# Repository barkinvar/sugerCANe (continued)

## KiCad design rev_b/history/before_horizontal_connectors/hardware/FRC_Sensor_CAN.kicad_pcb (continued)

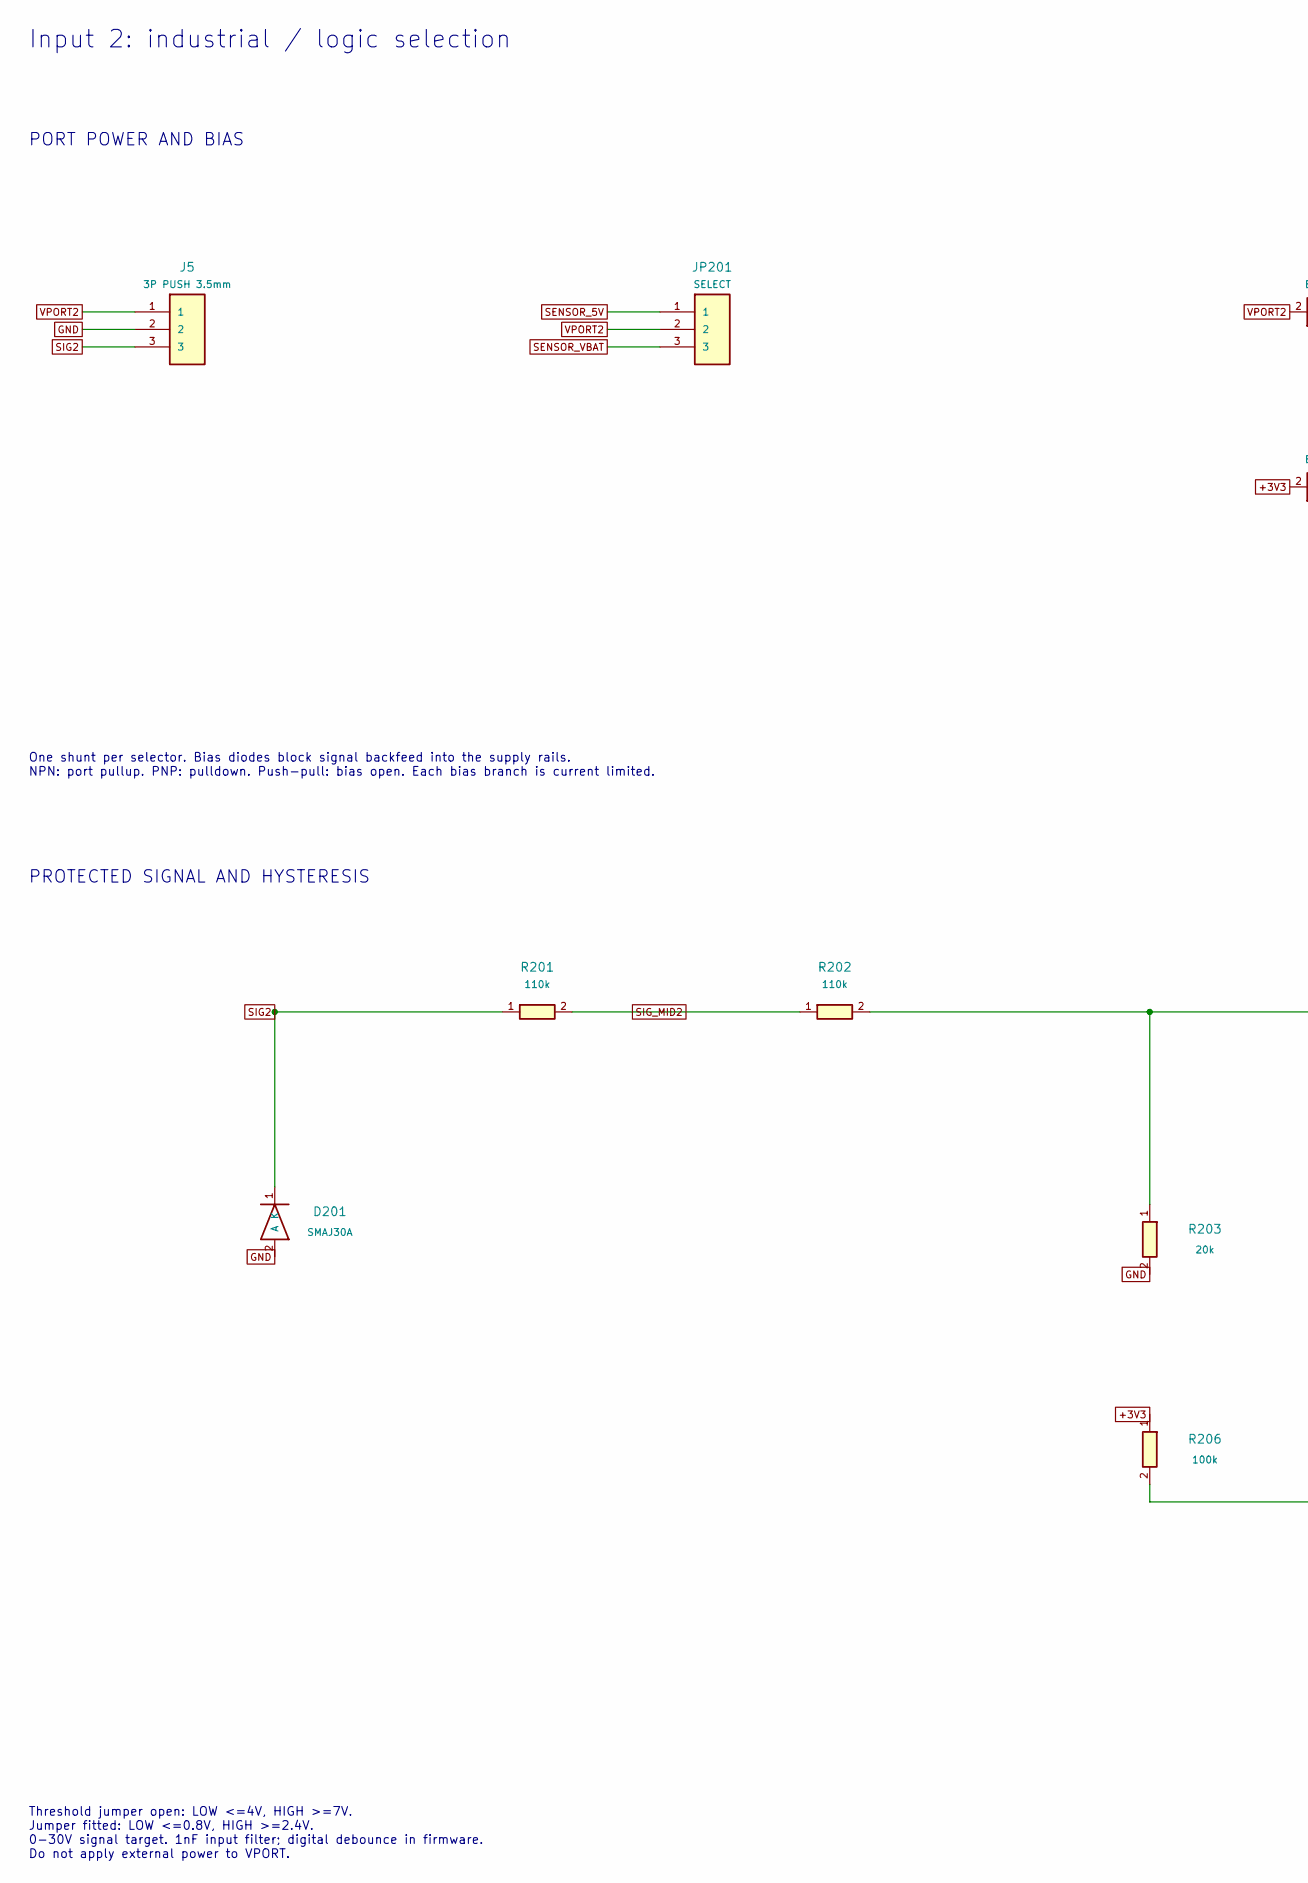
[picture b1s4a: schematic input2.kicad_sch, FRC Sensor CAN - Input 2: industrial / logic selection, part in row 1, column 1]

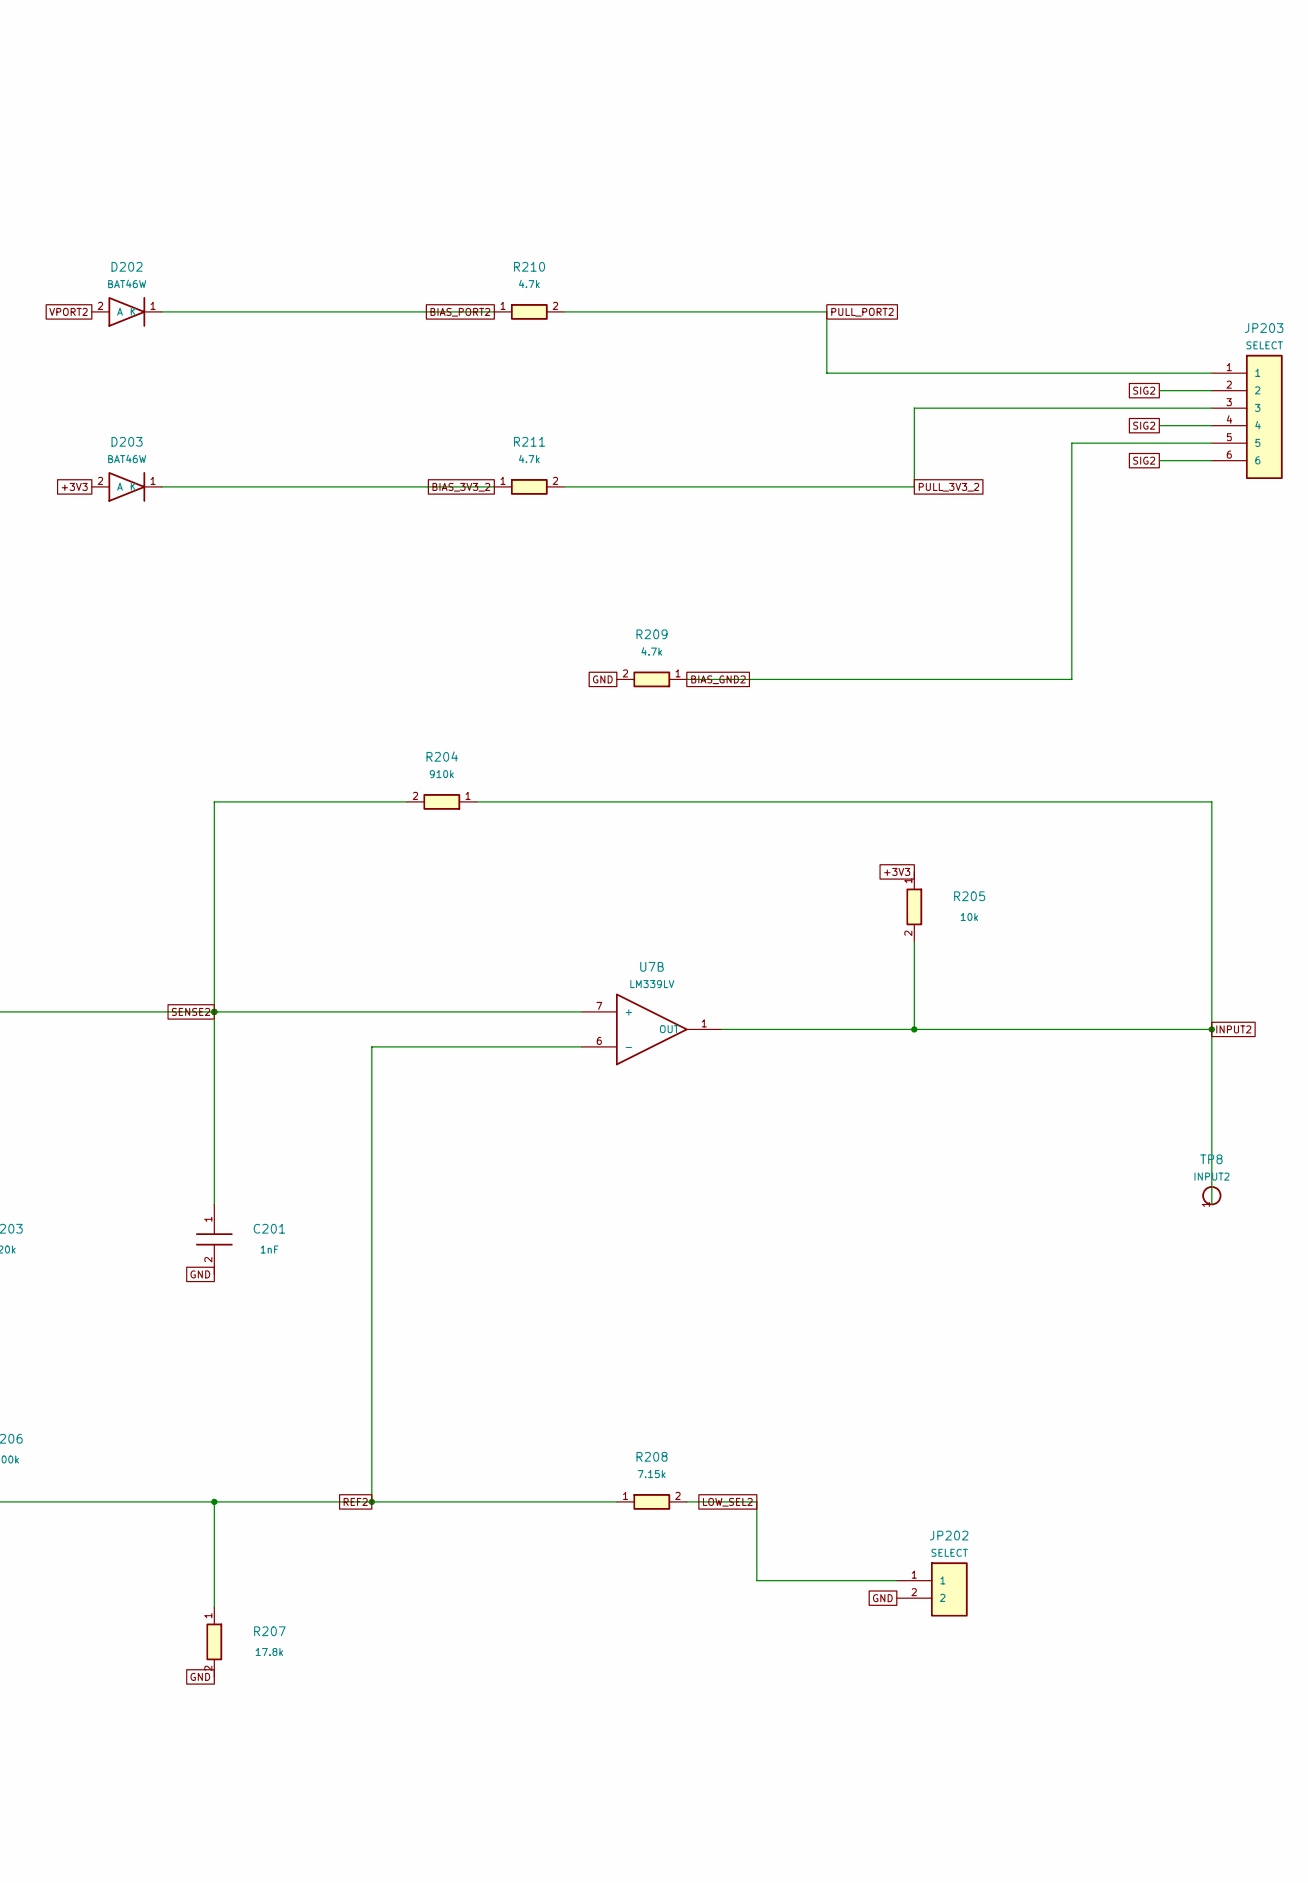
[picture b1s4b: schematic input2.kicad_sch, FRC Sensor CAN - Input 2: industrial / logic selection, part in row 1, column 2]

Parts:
C201: 1nF; C_0805_2012Metric; MPN CC0805JRNPO9BN102
D201: SMAJ30A; D_SMA; MPN SMAJ30A
D202, D203: BAT46W; D_SOD-123; MPN BAT46W-E3-18
J5: 3P PUSH 3.5mm; Weidmuller_LSF_135_3P; MPN 1885660000
JP201: SELECT; PinHeader_1x03_P2.00mm_Vertical; MPN M22-2010305
JP202: SELECT; PinHeader_1x02_P2.00mm_Vertical; MPN M22-2010205
JP203: SELECT; PinHeader_2x03_P2.00mm_Vertical; MPN M22-2020305
R201, R202: 110k; R_0805_2012Metric; MPN RC0805FR-07110KL
R203: 20k; R_0805_2012Metric; MPN RC0805FR-0720KL
R204: 910k; R_0805_2012Metric; MPN RC0805FR-07910KL
R205: 10k; R_0805_2012Metric; MPN RC0805FR-0710KL
R206: 100k; R_0805_2012Metric; MPN RC0805FR-07100KL
R207: 17.8k; R_0805_2012Metric; MPN ERJ-6ENF1782V
R208: 7.15k; R_0805_2012Metric; MPN RC0805FR-077K15L
R209: 4.7k; R_2010_5025Metric; MPN RC2010FK-074K7L
R210, R211: 4.7k; R_0805_2012Metric; MPN RC0805FR-074K7L
TP8: INPUT2; TestPoint_Pad_D2.0mm
U7: LM339LV; SOIC-14_3.9x8.7mm_P1.27mm; MPN LM339LVDR

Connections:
+3V3: D203.2 (A), R205.1, R206.1; also elsewhere on the board
BIAS_3V3_2: D203.1 (K), R211.1
BIAS_GND2: JP203.5, R209.1
BIAS_PORT2: D202.1 (K), R210.1
GND: C201.2, D201.2 (A), J5.2, JP202.2, R203.2, R207.2, R209.2; also elsewhere on the board
INPUT2: R204.1, R205.2, TP8.1, U7.1 (OUT); also elsewhere on the board
LOW_SEL2: JP202.1, R208.2
PULL_3V3_2: JP203.3, R211.2
PULL_PORT2: JP203.1, R210.2
REF2: R206.2, R207.1, R208.1, U7.6 (-)
SENSE2: C201.1, R202.2, R203.1, R204.2, U7.7 (+)
SENSOR_5V: JP201.1; also elsewhere on the board
SENSOR_VBAT: JP201.3; also elsewhere on the board
SIG2: D201.1 (K), J5.3, JP203.2, JP203.4, JP203.6, R201.1
SIG_MID2: R201.2, R202.1
VPORT2: D202.2 (A), J5.1, JP201.2

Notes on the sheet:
Input 2: industrial / logic selection
PORT POWER AND BIAS
One shunt per selector. Bias diodes block signal backfeed into the supply rails. NPN: port pullup. PNP: pulldown. Push-pull: bias open. Each bias branch is current limited.
PROTECTED SIGNAL AND HYSTERESIS
Threshold jumper open: LOW <=4V, HIGH >=7V. Jumper fitted: LOW <=0.8V, HIGH >=2.4V. 0-30V signal target. 1nF input filter; digital debounce in firmware. Do not apply external power to VPORT.

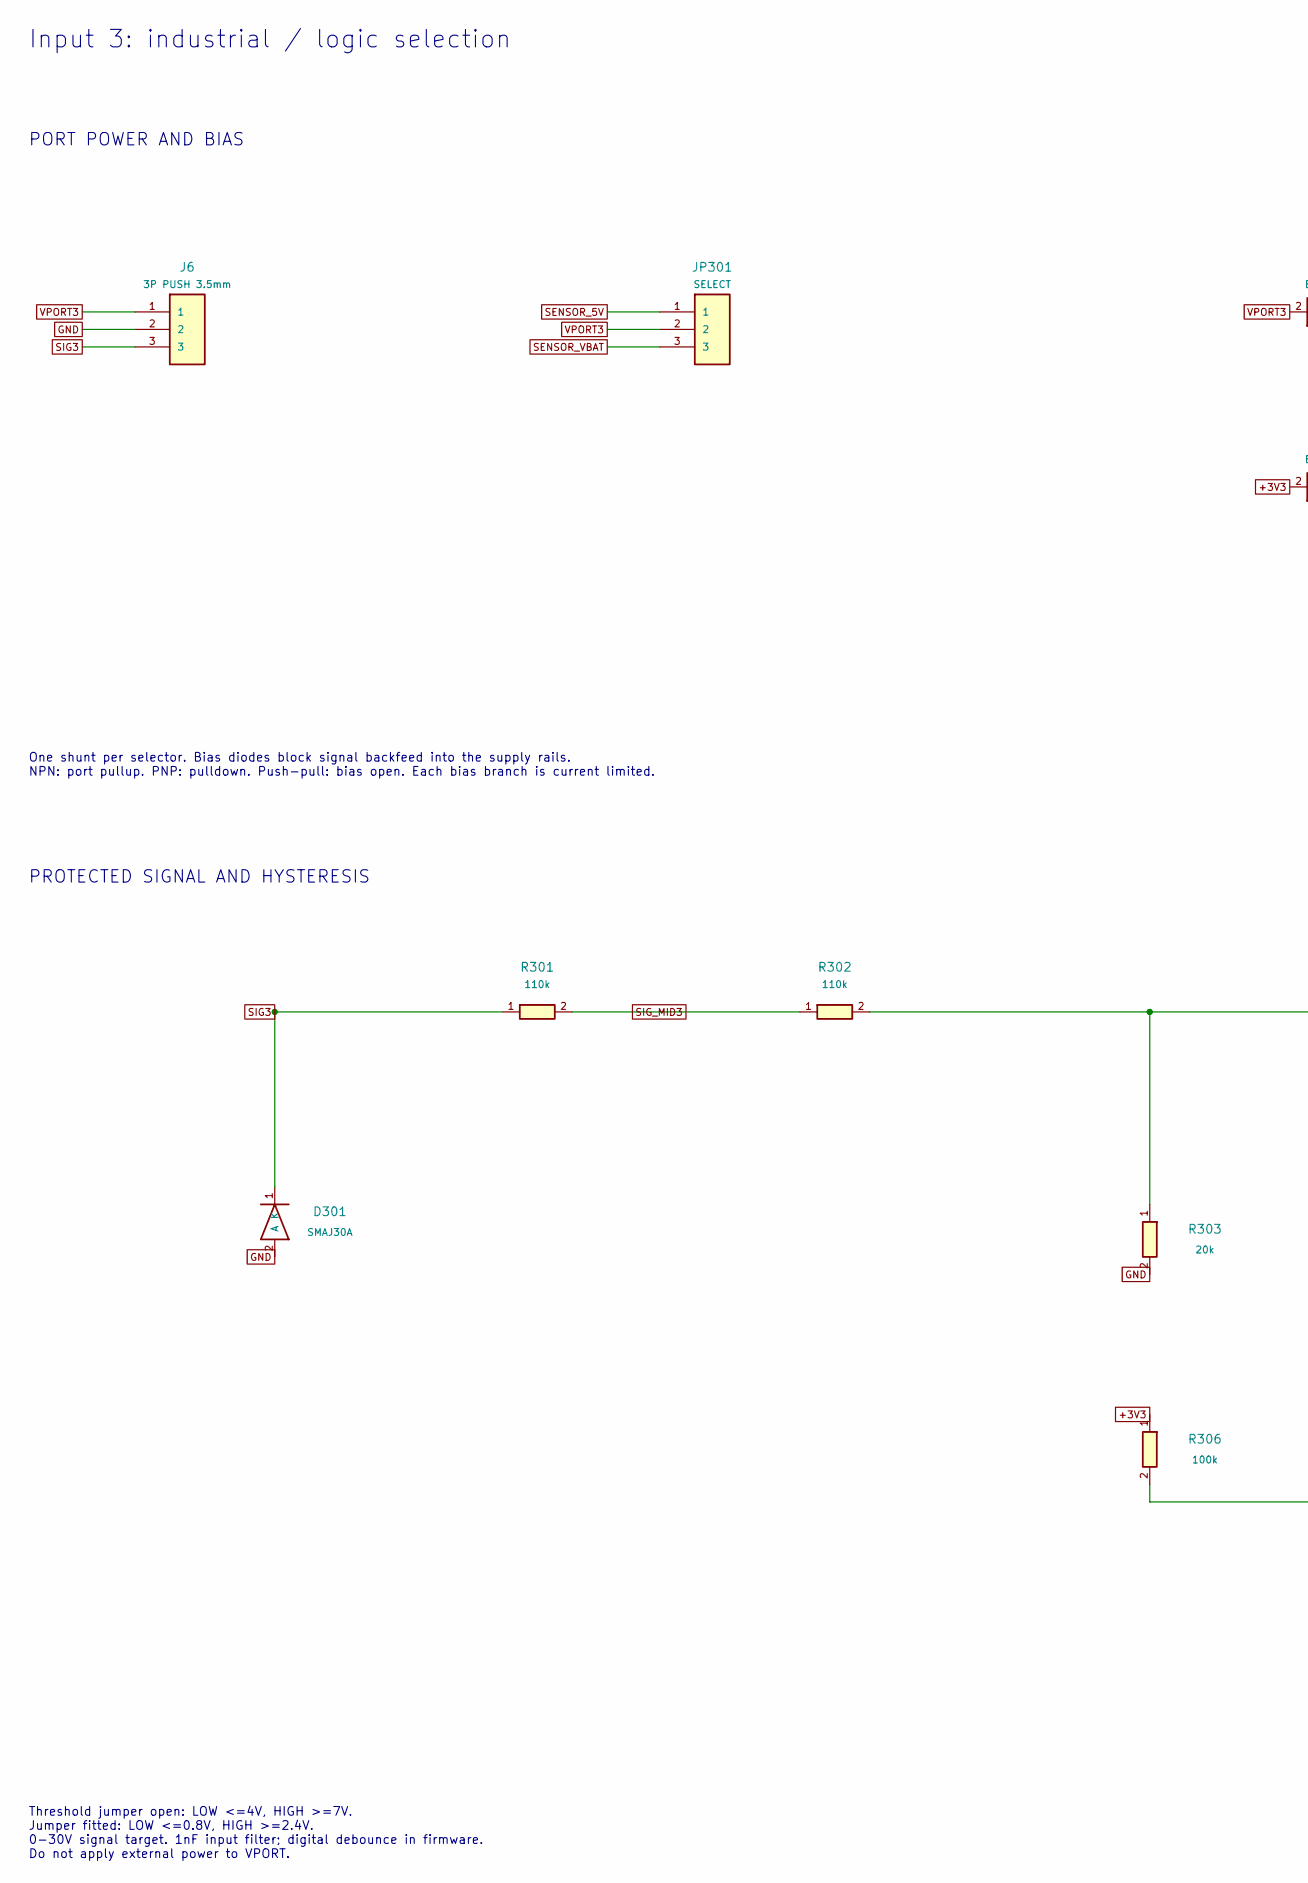
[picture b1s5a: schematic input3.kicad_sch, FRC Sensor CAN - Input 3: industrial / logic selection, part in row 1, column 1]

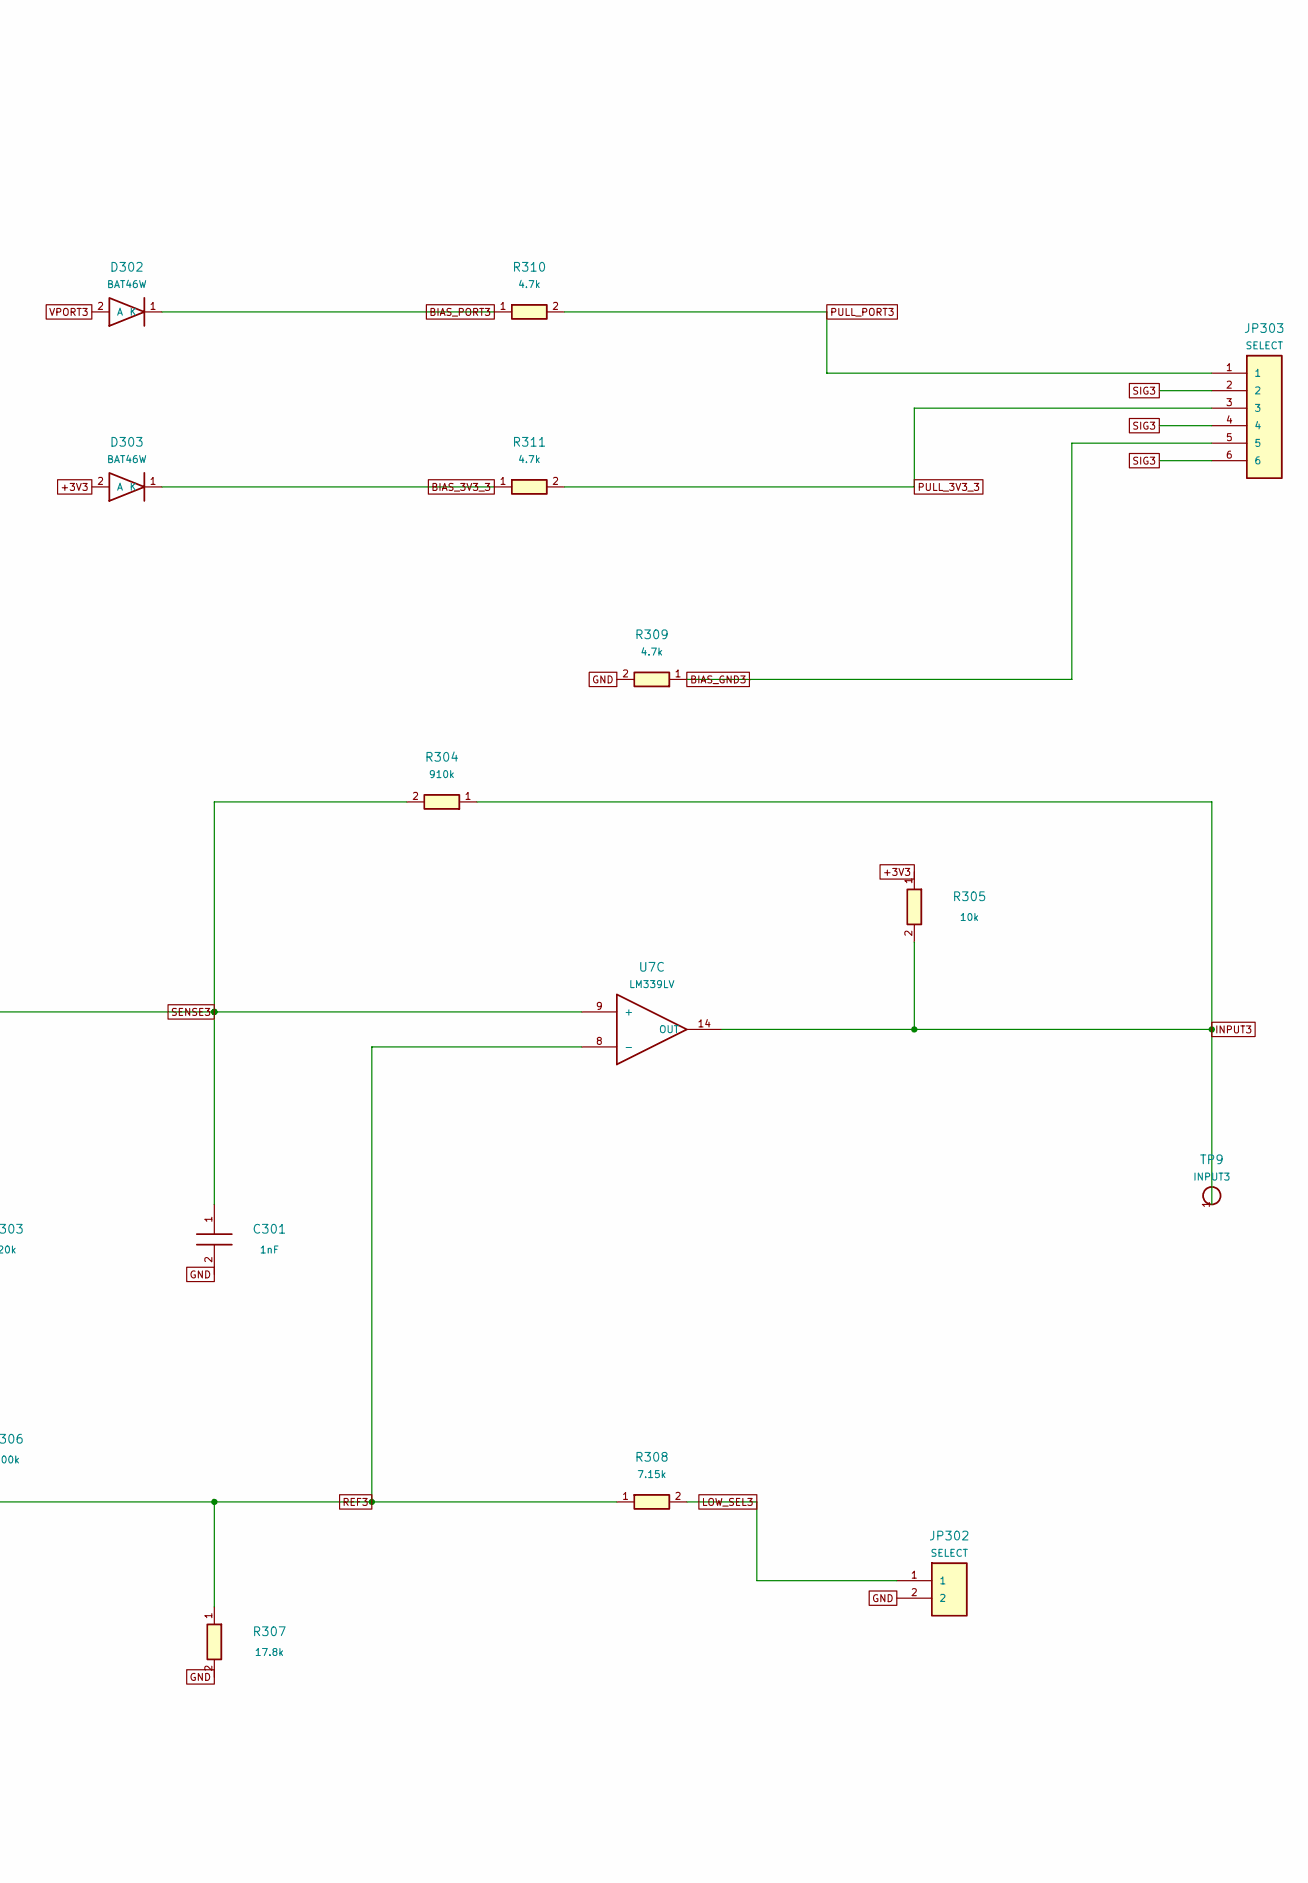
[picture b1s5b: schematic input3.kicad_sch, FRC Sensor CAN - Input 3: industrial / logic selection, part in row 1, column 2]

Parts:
C301: 1nF; C_0805_2012Metric; MPN CC0805JRNPO9BN102
D301: SMAJ30A; D_SMA; MPN SMAJ30A
D302, D303: BAT46W; D_SOD-123; MPN BAT46W-E3-18
J6: 3P PUSH 3.5mm; Weidmuller_LSF_135_3P; MPN 1885660000
JP301: SELECT; PinHeader_1x03_P2.00mm_Vertical; MPN M22-2010305
JP302: SELECT; PinHeader_1x02_P2.00mm_Vertical; MPN M22-2010205
JP303: SELECT; PinHeader_2x03_P2.00mm_Vertical; MPN M22-2020305
R301, R302: 110k; R_0805_2012Metric; MPN RC0805FR-07110KL
R303: 20k; R_0805_2012Metric; MPN RC0805FR-0720KL
R304: 910k; R_0805_2012Metric; MPN RC0805FR-07910KL
R305: 10k; R_0805_2012Metric; MPN RC0805FR-0710KL
R306: 100k; R_0805_2012Metric; MPN RC0805FR-07100KL
R307: 17.8k; R_0805_2012Metric; MPN ERJ-6ENF1782V
R308: 7.15k; R_0805_2012Metric; MPN RC0805FR-077K15L
R309: 4.7k; R_2010_5025Metric; MPN RC2010FK-074K7L
R310, R311: 4.7k; R_0805_2012Metric; MPN RC0805FR-074K7L
TP9: INPUT3; TestPoint_Pad_D2.0mm
U7: LM339LV; SOIC-14_3.9x8.7mm_P1.27mm; MPN LM339LVDR

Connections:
+3V3: D303.2 (A), R305.1, R306.1; also elsewhere on the board
BIAS_3V3_3: D303.1 (K), R311.1
BIAS_GND3: JP303.5, R309.1
BIAS_PORT3: D302.1 (K), R310.1
GND: C301.2, D301.2 (A), J6.2, JP302.2, R303.2, R307.2, R309.2; also elsewhere on the board
INPUT3: R304.1, R305.2, TP9.1, U7.14 (OUT); also elsewhere on the board
LOW_SEL3: JP302.1, R308.2
PULL_3V3_3: JP303.3, R311.2
PULL_PORT3: JP303.1, R310.2
REF3: R306.2, R307.1, R308.1, U7.8 (-)
SENSE3: C301.1, R302.2, R303.1, R304.2, U7.9 (+)
SENSOR_5V: JP301.1; also elsewhere on the board
SENSOR_VBAT: JP301.3; also elsewhere on the board
SIG3: D301.1 (K), J6.3, JP303.2, JP303.4, JP303.6, R301.1
SIG_MID3: R301.2, R302.1
VPORT3: D302.2 (A), J6.1, JP301.2

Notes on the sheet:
Input 3: industrial / logic selection
PORT POWER AND BIAS
One shunt per selector. Bias diodes block signal backfeed into the supply rails. NPN: port pullup. PNP: pulldown. Push-pull: bias open. Each bias branch is current limited.
PROTECTED SIGNAL AND HYSTERESIS
Threshold jumper open: LOW <=4V, HIGH >=7V. Jumper fitted: LOW <=0.8V, HIGH >=2.4V. 0-30V signal target. 1nF input filter; digital debounce in firmware. Do not apply external power to VPORT.

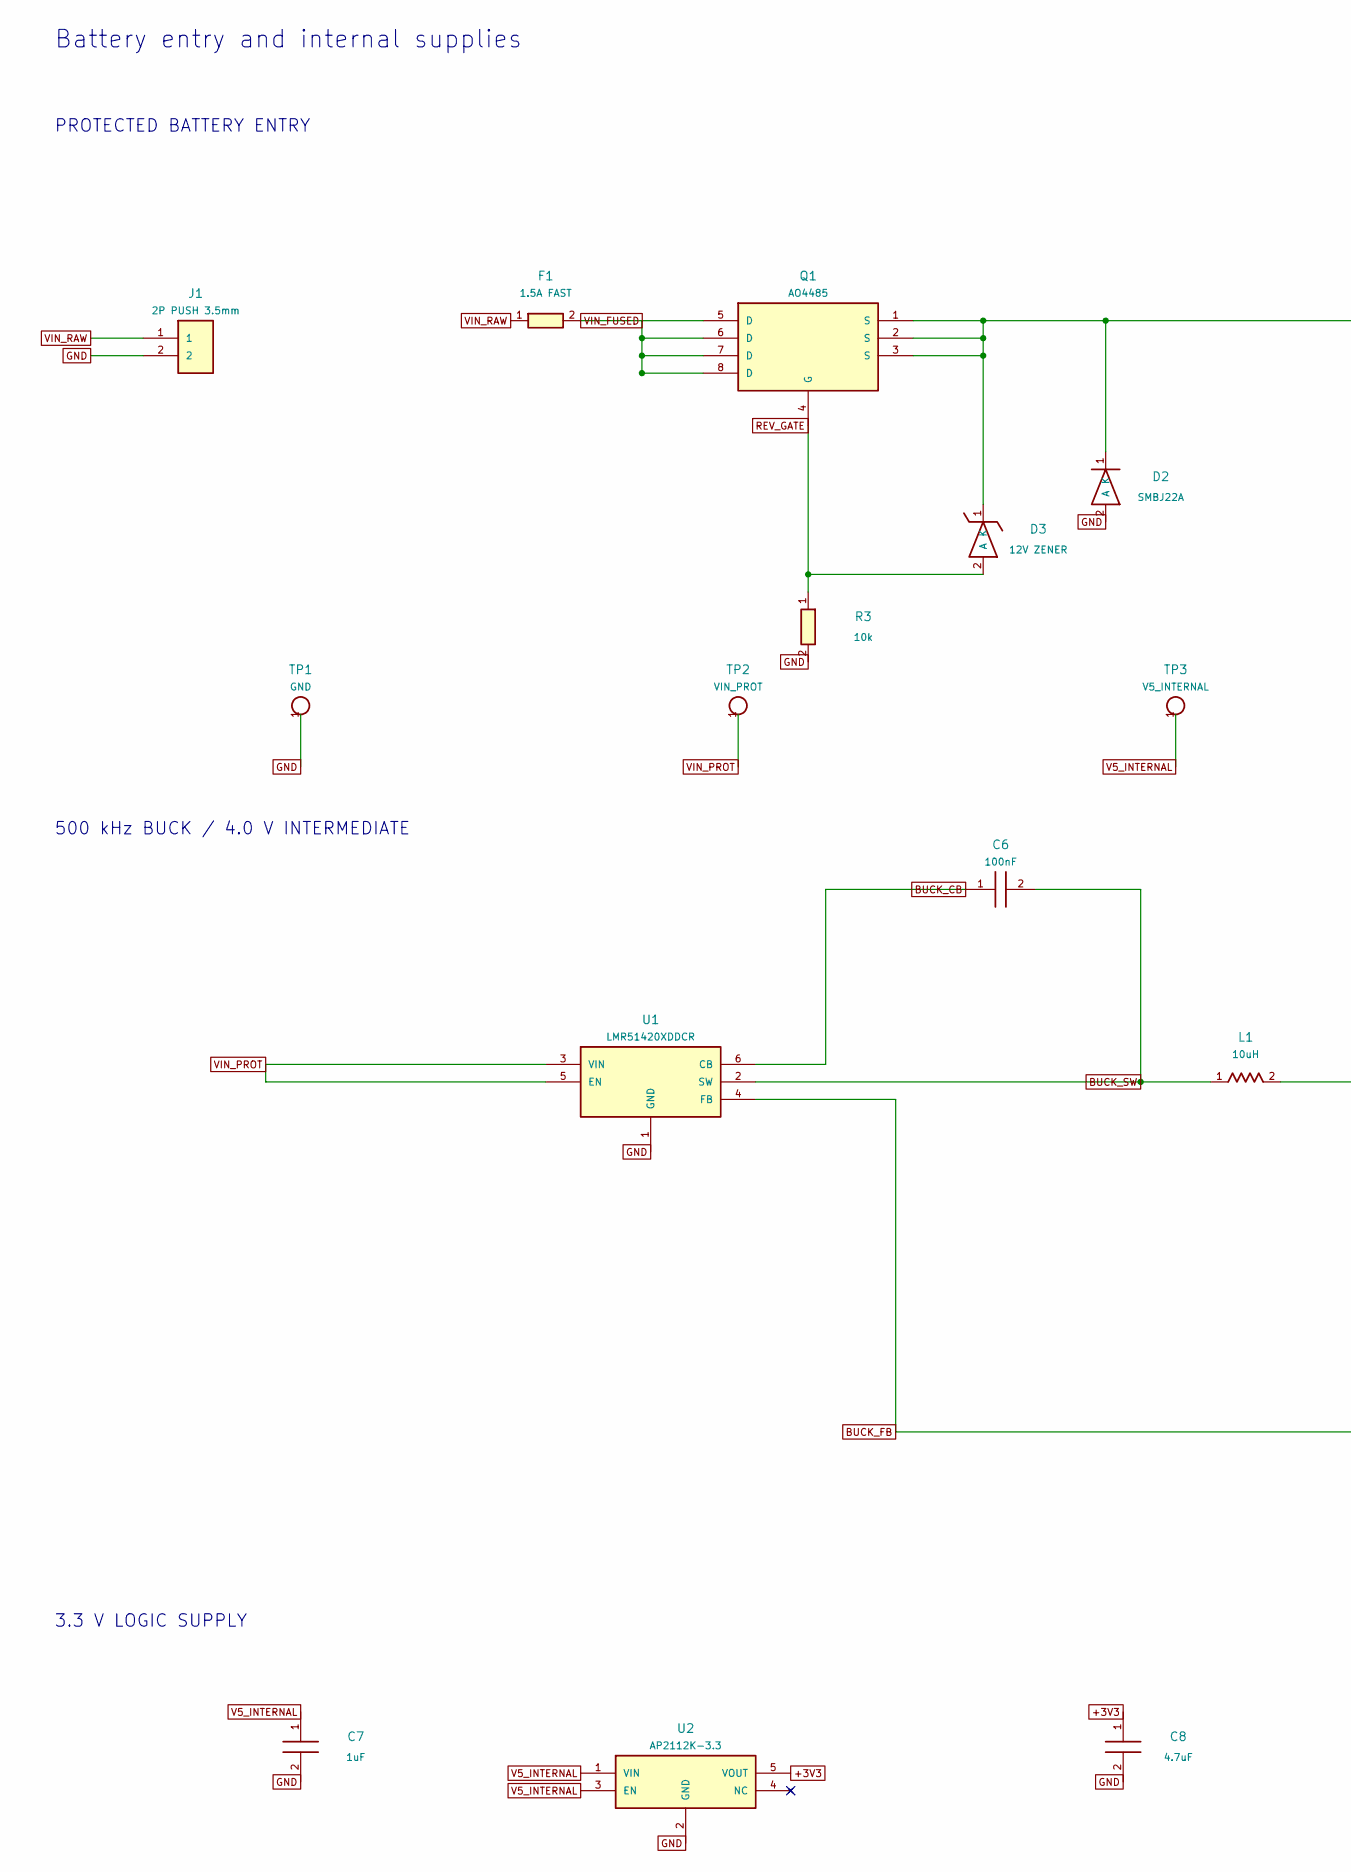
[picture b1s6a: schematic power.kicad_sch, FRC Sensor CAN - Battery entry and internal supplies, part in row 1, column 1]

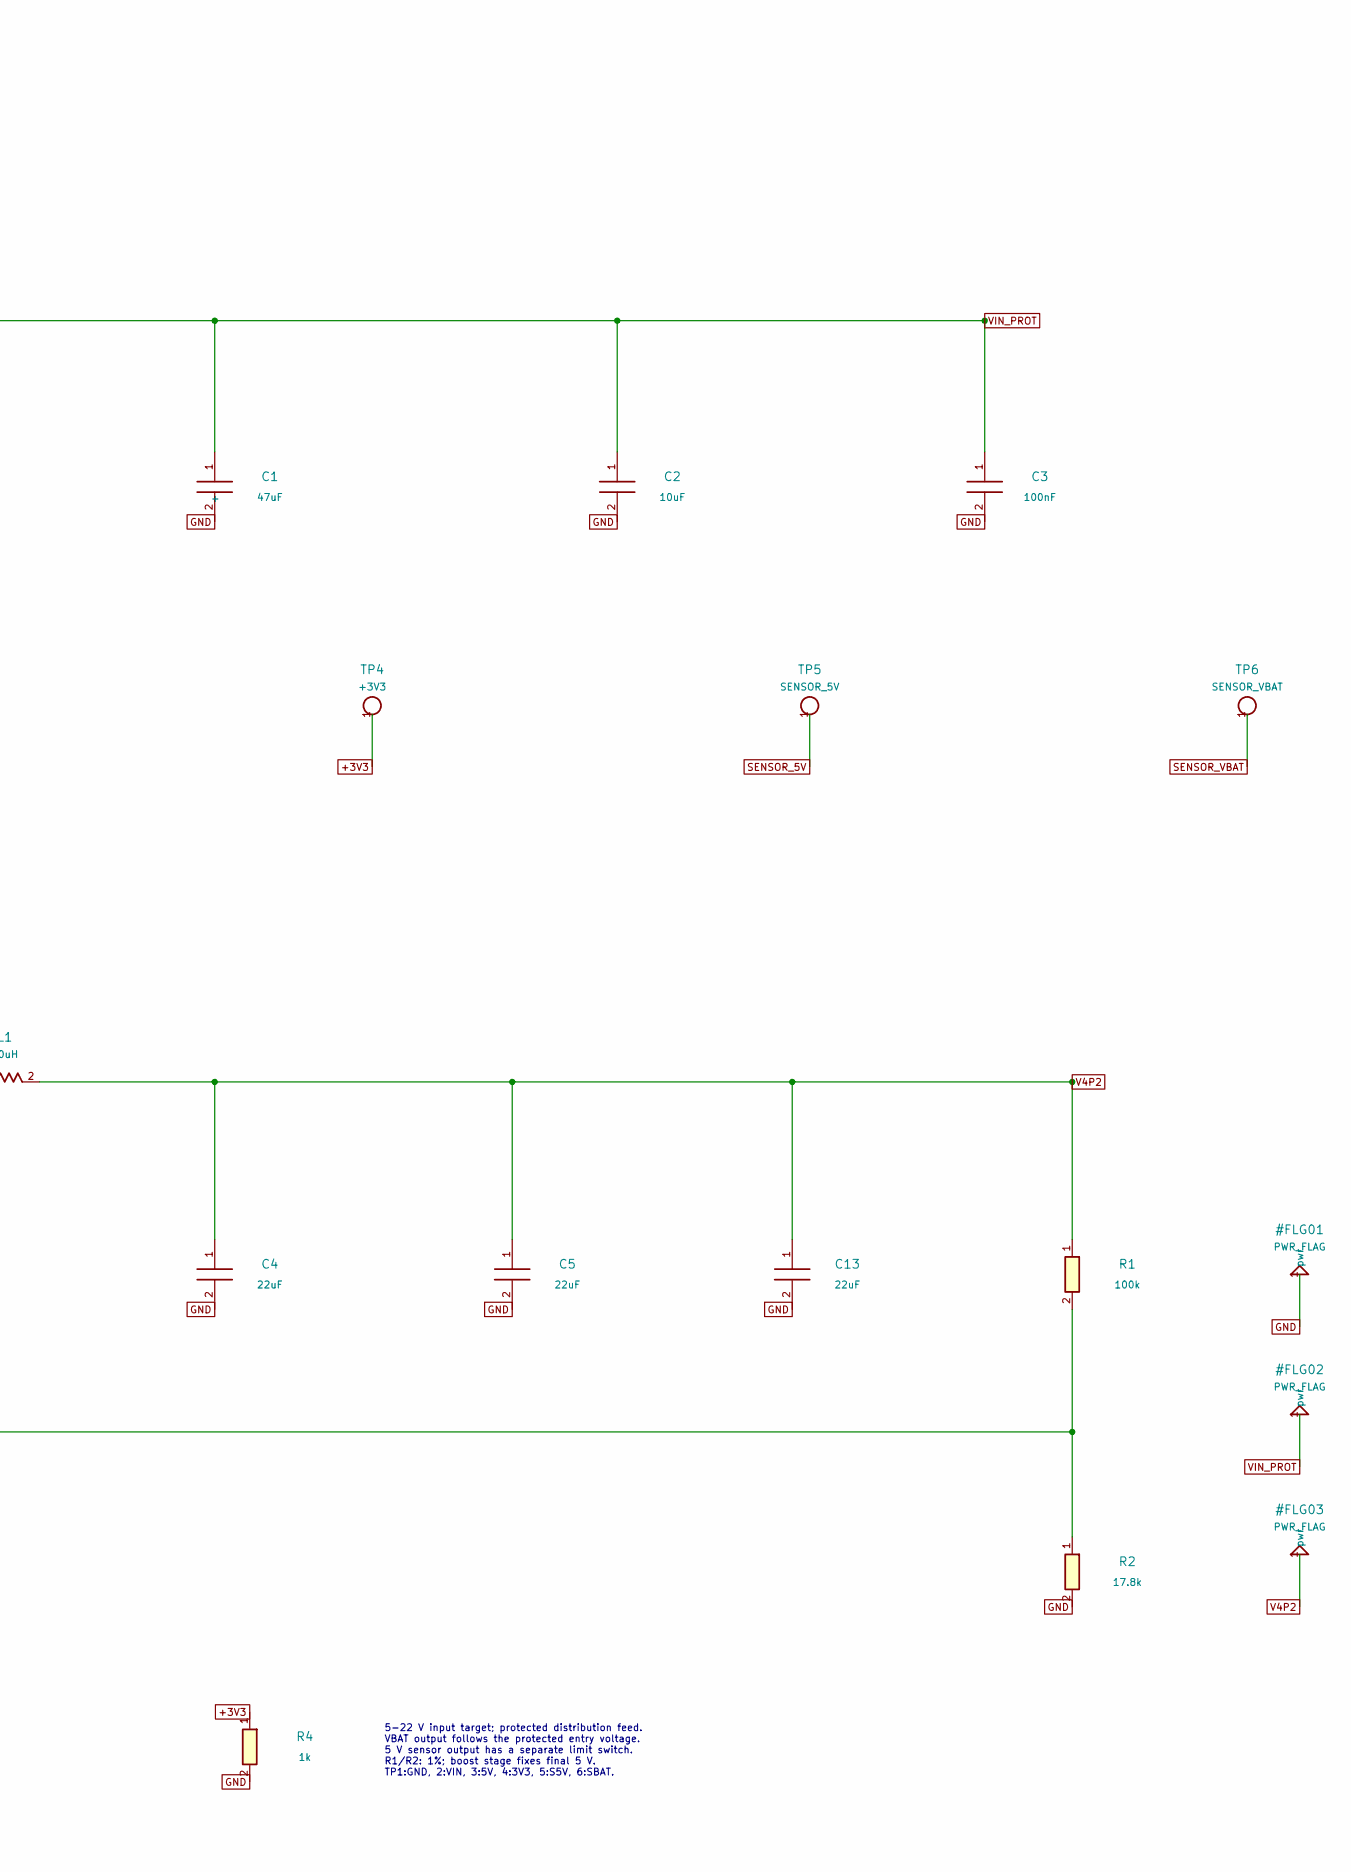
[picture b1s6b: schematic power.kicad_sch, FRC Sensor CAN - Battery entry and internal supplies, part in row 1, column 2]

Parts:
C1: 47uF; CP_Elec_8x6.5; MPN EEE-FK1H470P
C2: 10uF; C_1210_3225Metric; MPN CL32B106KBJNNWE
C3, C6: 100nF; C_0805_2012Metric; MPN CC0805KRX7R9BB104
C4, C5, C13: 22uF; C_1206_3216Metric; MPN CL31A226KAHNNNE
C7: 1uF; C_0805_2012Metric; MPN CC0805KKX7R9BB105
C8: 4.7uF; C_0805_2012Metric; MPN TMK212AB7475KG-T
D2: SMBJ22A; D_SMB; MPN SMBJ22A-E3/52
D3: 12V ZENER; D_SOD-123; MPN MMSZ12T1G
F1: 1.5A FAST; Fuse_Littelfuse-NANO2-451_453; MPN 045101.5MRL
J1: 2P PUSH 3.5mm; Weidmuller_LSF_135_2P; MPN 1885650000
L1: 10uH; L_Bourns_SRP7028A_7.3x6.6mm; MPN SRP7028A-100M
Q1: AO4485; SOIC-8_3.9x4.9mm_P1.27mm; MPN AO4485
R1: 100k; R_0805_2012Metric; MPN RC0805FR-07100KL
R2: 17.8k; R_0805_2012Metric; MPN ERJ-6ENF1782V
R3: 10k; R_0805_2012Metric; MPN RC0805FR-0710KL
R4: 1k; R_0805_2012Metric; MPN RC0805FR-071KL
TP1: GND; TestPoint_Pad_D2.0mm
TP2: VIN_PROT; TestPoint_Pad_D2.0mm
TP3: V5_INTERNAL; TestPoint_Pad_D2.0mm
TP4: +3V3; TestPoint_Pad_D2.0mm
TP5: SENSOR_5V; TestPoint_Pad_D2.0mm
TP6: SENSOR_VBAT; TestPoint_Pad_D2.0mm
U1: LMR51420XDDCR; TSOT-23-6; MPN LMR51420XDDCR
U2: AP2112K-3.3; SOT-23-5; MPN AP2112K-3.3TRG1

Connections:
+3V3: C8.1, R4.1, TP4.1, U2.5 (VOUT); also elsewhere on the board
BUCK_CB: C6.1, U1.6 (CB)
BUCK_FB: R1.2, R2.1, U1.4 (FB)
BUCK_SW: C6.2, L1.1, U1.2 (SW)
GND: C1.2, C2.2, C3.2, C4.2, C5.2, C7.2, C8.2, C13.2, D2.2 (A), J1.2, R2.2, R3.2, R4.2, TP1.1, U1.1 (GND), U2.2 (GND); also elsewhere on the board
REV_GATE: D3.2 (A), Q1.4 (G), R3.1
SENSOR_5V: TP5.1; also elsewhere on the board
SENSOR_VBAT: TP6.1; also elsewhere on the board
V4P2: C4.1, C5.1, C13.1, L1.2, R1.1; also elsewhere on the board
V5_INTERNAL: C7.1, TP3.1, U2.1 (VIN), U2.3 (EN); also elsewhere on the board
VIN_FUSED: F1.2, Q1.5 (D), Q1.6 (D), Q1.7 (D), Q1.8 (D)
VIN_PROT: C1.1 (+), C2.1, C3.1, D2.1 (K), D3.1 (K), Q1.1 (S), Q1.2 (S), Q1.3 (S), TP2.1, U1.3 (VIN), U1.5 (EN); also elsewhere on the board
VIN_RAW: F1.1, J1.1

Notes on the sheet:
Battery entry and internal supplies
PROTECTED BATTERY ENTRY
500 kHz BUCK / 4.0 V INTERMEDIATE
3.3 V LOGIC SUPPLY
5-22 V input target; protected distribution feed. VBAT output follows the protected entry voltage. 5 V sensor output has a separate limit switch. R1/R2: 1%; boost stage fixes final 5 V. TP1:GND, 2:VIN, 3:5V, 4:3V3, 5:S5V, 6:SBAT.
